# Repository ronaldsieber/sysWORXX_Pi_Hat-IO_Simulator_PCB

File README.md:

# sysWORXX Pi HAT / IO Simulator

**KiCad Projekt des IO Simulator HAT für den sysWORXX Pi-AM62x.**

Der *IO Simulator HAT* stellt verschiedene Peripherie-Elemente bereit, um Experimente sowie Test- und Inbetriebnahme von Softwareprojekten auf dem *sysWORXX Pi-AM62x* zu vereinfachen.

## IO Simulator HAT Features

Der *IO Simulator HAT* umfasst folgende Peripherie-Elemente:
- 6x Digital Input (4x Push-Button, 2x DIP Switch)
- 4x Digital Output (LED)
- 2x Analog Input (2x Poti, via MCP3202 auf dem HAT)

![\[kicad_3d_model\]](Documentation/sysWORXX_Pi_Hat-IO_Simulator_PCB.3d-model.png)

## sysWORXX Pi-AM62x

Der *sysWORXX Pi-AM62x* ist ein Linux-basierter Einplatinencomputer (SBC), mit dem sich unter anderem Proof-of-Concepts schnell und einfach realisieren lassen. Er ähnelt dem Raspberry Pi, unterstützt aber insbesondere industrielle Anforderungen (2x ETH, SDcard + eMMC, RTC, CAN-FD/TTL, Linux Konsole via on-board FTDI USB-UART-Interface):

Hersteller Seite:
https://www.systec-electronic.com/sysworxx-pi-am62x

Bezugsquelle:
https://www.conrad.de/de/p/evaluation-board-sysworxx-pi-am62x-4core-2gb-ram-32gb-emmc-931380946.html

![\[sysWORXX Pi-AM62x\]](Documentation/sysWORXX_Pi_AM62x.png)

Der sysWORXX Pi-AM62x unterstützt u.a. folgende Programmiersprachen:
- C/C++
- Rust
- C#
- Java
- Python
- Node-RED
- IEC 61131-3

## IO Simulator HAT

Der *IO Simulator HAT* basiert auf einer vierlagigen Leiterplatte im typischen Raspberry Pi HAT Format (64x56 mm). Die Platine ist einseitig bestückt und verwendet nur sehr einfach zu lötende THT Bauteile (Through Hole Technology). Der *IO Simulator HAT* kann somit leicht auch von Schülern und Bastlern mit etwas Löterfahrung aufgebaut werden.

Die Werte aller Bauteile sind im [Schaltplan](Documentation/sysWORXX_Pi_Hat-IO_Simulator_PCB_Schematic.pdf) spezifiziert.

![\[sysWORXX IO Simulator\]](Documentation/sysWORXX_Pi_Hat-IO_Simulator_PCB.png)

**KiCad Schaltplansymbole und Footprints**

Für den *IO Simulator HAT* wurden einige Schaltplansymbole und Footprints neu erstellt bzw. modifiziert. Diese sind im Repository im Zweig [KiCad_Components/usrlib](KiCad_Components/usrlib) abgelegt.

**Bezugsquellen**

In der [Stückliste](Documentation/sysWORXX_Pi_Hat-IO_Simulator_PCB_BoM.pdf) (BoM, Bill of Material) sind für alle Komponenten mögliche Bezugsquellen (incl. Bestellnummer) angegeben. Bei einer Suche im Internet findet man zudem leicht mehrere PCB Hersteller, die direkt das KiCad Layout File [sysWORXX_Pi_Hat-IO_Simulator_PCB.kicad_pcb](sysWORXX_Pi_Hat-IO_Simulator_PCB/sysWORXX_Pi_Hat-IO_Simulator_PCB.kicad_pcb) importieren können. Die PCBs erhält man dann mit Bestückungsdruck auf der Oberseite nach wenigen Tagen per Post zugeschickt. Eine mögliche direkte Bezugsquelle der Platine ist z.B. hier:

https://aisler.net/p/XVLIPALV

## Device Tree für IO Simulator HAT

Der *sysWORXX Pi-AM62x* unterstützt verschiedene IO-Belegung für den 40poligen Pin-Header. Die Steuerung des Pin-Muxings erfolgt Linux-typisch mit Hilfe des Device Trees, zusammen mit Device Tree Overlays (DTBO), die separat geladen werden können. Um die für den IO Simulator HAT notwendige IO-Belegung bereitzustellen, ist das entsprechende `IO Simulator HAT Overlay` zu aktivieren. Dazu sind als Benutzer `root` folgende Befehle auszuführen:

    sudo dtbo-setup set k3-am625-systec-sysworxx-pi-hat-io-simulator.dtbo
    reboot

Neben der Bereitstellung der digitalen IO's sorgt das Overlay auch dafür, dass die für den 12Bit ADC (MCP3202) notwendigen Treiber geladen werden, um die beiden analogen Eingänge AI0 und AI1 lesen zu können.

Die digitalen Ein- und Ausgänge (DI0..DI5, DO0..DO3) lassen sich am einfachsten über den [sysWORXX IO Treiber](https://github.com/systec-electronic/sysworxx-io) ansprechen. Dieser ist bereits im Image des sysWORXX Pi-AM62x enthalten und wird z.B. von Node-RED automatisch geladen. In Node-RED wird die entsprechende Funktionalität über die Nodes `Digital In` bzw. `Digital Out` abgebildet.

Die Werte der beiden anlogen Eingänge AI0 und AI1 müssen dagegen direkt aus dem SysFS gelesen werden:

    cat /sys/bus/iio/devices/iio:device0/in_voltage0_raw
    cat /sys/bus/iio/devices/iio:device0/in_voltage1_raw

In Node-RED kann hierzu der Node `read file` genutzt werden. Der Node ist für AI0 wie folgt zu konfigurieren (siehe Tab `sysWORXX PI Analog In` im Beispiel-Flow [IO-HAT_Periphery.json](Node-RED_Flow/IO-HAT_Periphery.json) des nachfolgenden Abschnitts):

    Dateiname -> Path -> /sys/bus/iio/devices/iio:device0/in_voltage0_raw

Um AI1 zu lesen, ist der Kanalbezeichner `in_voltage0_raw` entsprechend durch `in_voltage1_raw` zu ersetzen. Sollen beide Kanäle in einer Applikation genutzt werden, muss der Zugriff sequentiell mit einer kurzen Lesepause zwischen den beiden Kanälen erfolgen. Erfolgt der Lesezugriff überlappend, führt dies zu Fehlern. Die Kanäle liefern in diesem Fall den Wert 0.

## Node-RED Inbetriebnahme-Software

Test- und Inbetriebnahme des *IO Simulator HAT* sind mit dem Node-RED Flow [IO-HAT_Periphery.json](Node-RED_Flow/IO-HAT_Periphery.json) sehr einfach möglich. Er bedient alle Komponenten des Simulators und stellt die aktuellen Werte übersichtlich auf einem Dashboard dar.

![\[Node-RED Inbetriebnahme Flow - Digital In/Out\]](Documentation/Node-RED_Flow_DIO.png)

Der Tab `sysWORXX PI Analog In` verdeutlicht den Zugriff auf die beiden analogen Eingänge. Das Lesen des ersten Kanals AI0 wird durch den `inject` Node im Sekundentakt getriggert. Den Analogwert selbst liest der nachfolgende Node `read file` direkt aus dem SysFS. Das Lesen des zweiten Kanals erfolgt zeitversetzt mit einer Verzögerung von 250ms, realisiert durch den Node vom Typ `delay`.

![\[Node-RED Inbetriebnahme Flow - Analog In\]](Documentation/Node-RED_Flow_AI.png)

Der Node-RED Flow [IO-HAT_Periphery.json](Node-RED_Flow/IO-HAT_Periphery.json) ist wie folgt in das Node-RED auf dem *sysWORXX Pi-AM62x* zu importieren:

    Node-RED Menu -> Import -> Zwischenablage -> Button "Select a File to Import"

Nach dem Deploy auf den *sysWORXX Pi-AM62x* wird der Flow auf dem Gerät ausgeführt und das Node-RED Dashboard visualisiert die aktuellen Werte der IO-Peripherie.

![\[Node-RED Dashboard\]](Documentation/Node-RED_Dashboard.png)

## Verwendete Komponenten von Drittanbietern

1. **PCB Shape + Steckverbinder Footprints**

Das PCB Shape und die Footprints für den 40poligen Steckverbinder wurden übernommen von:
https://github.com/wrongbaud/RPi_Hat_Template

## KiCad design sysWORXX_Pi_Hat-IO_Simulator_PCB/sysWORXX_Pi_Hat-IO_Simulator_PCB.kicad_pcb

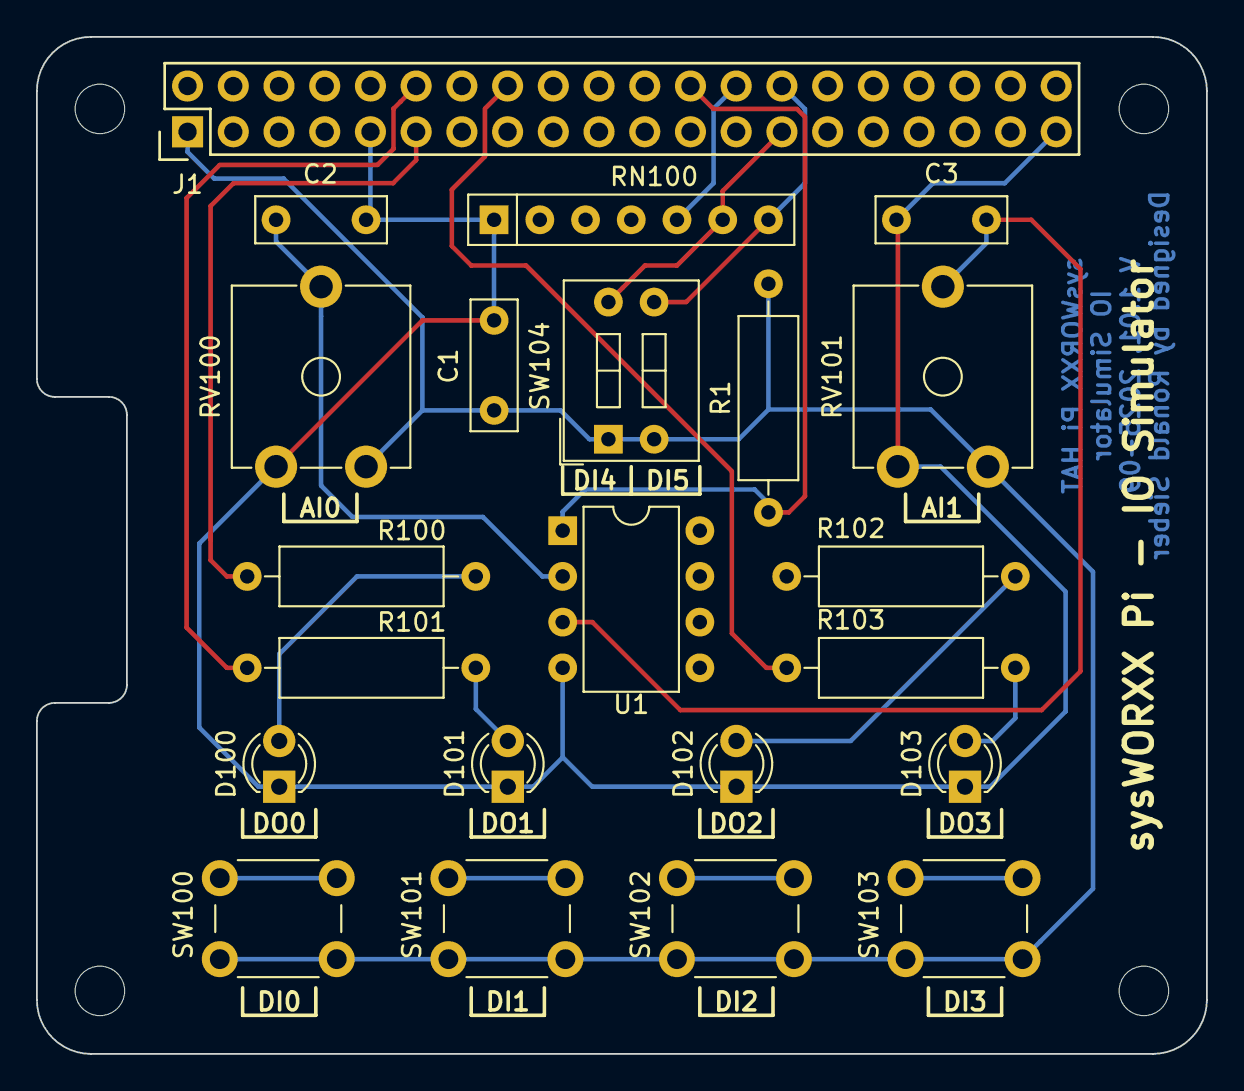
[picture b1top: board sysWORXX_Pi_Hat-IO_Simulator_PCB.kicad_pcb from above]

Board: 4 copper layers, 65.0 x 56.5 mm, 22 parts (0 on the bottom side), 22 nets.

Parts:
C1: 1µ; C_Rect_L7.2mm_W2.5mm_P5.00mm_FKS2_FKP2_MKS2_MKP2
C2, C3: 100n; C_Rect_L7.2mm_W2.5mm_P5.00mm_FKS2_FKP2_MKS2_MKP2
D100: DO0; LED_D3.0mm
D101: DO1; LED_D3.0mm
D102: DO2; LED_D3.0mm
D103: DO3; LED_D3.0mm
J1: sysWORXX_Pi_GPIO; Pin_Header_Straight_2x20
R1: 10k; R_Axial_DIN0309_L9.0mm_D3.2mm_P12.70mm_Horizontal
R100, R101, R102, R103: 270R; R_Axial_DIN0309_L9.0mm_D3.2mm_P12.70mm_Horizontal
RN100: SIL 7-6 4,7K; R_Array_SIP7
RV100, RV101: 4k7; Potentiometer_Trimmer_ACP_CA9v_Horizontal_Px10.0mm_Py5.0mm
SW100: DI0; SW_PUSH_6mm_h5mm
SW101: DI1; SW_PUSH_6mm_h5mm
SW102: DI2; SW_PUSH_6mm_h5mm
SW103: DI3; SW_PUSH_6mm_h5mm
SW104: DI3/DI4; SW_DIP_x2_W7.62mm_Slide
U1: MCP3202; DIP-8_W7.62mm

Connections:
unnamed: C1.1, C2.1, C3.1, D100.1, D101.1, D102.1, D103.1, J1.9, J1.39, RN100.1, RV100.3, RV101.3, U1.4
unnamed: C1.2, J1.1, R1.2, RV100.1, RV101.1, SW100.2, SW101.2, SW102.2, SW103.2, SW104.1, SW104.2, U1.8
unnamed: C2.2, RV100.2, U1.2
unnamed: C3.2, RV101.2, U1.3
unnamed: D100.2, R100.2
unnamed: D101.2, R101.2
unnamed: D102.2, R102.2
unnamed: D103.2, R103.2
unnamed: J1.7, RN100.2, SW100.1
unnamed: J1.11, R100.1
unnamed: J1.12, R101.1
unnamed: J1.13, RN100.3, SW101.1
unnamed: J1.15, R102.1
unnamed: J1.16, R103.1
unnamed: J1.18, RN100.4, SW102.1
unnamed: J1.19, U1.5
unnamed: J1.21, U1.6
unnamed: J1.23, U1.7
unnamed: J1.24, R1.1, U1.1
unnamed: J1.26, RN100.5, SW103.1
unnamed: J1.27, RN100.6, SW104.4
unnamed: J1.28, RN100.7, SW104.3
